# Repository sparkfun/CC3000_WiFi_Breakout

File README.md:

CC3000_WiFi_Breakout
====================

[  
*CC3000 WiFi Breakout Board (WRL-12072)*](https://www.sparkfun.com/products/12072)

WiFi breakout board for the [TI CC3000 module](http://www.ti.com/product/cc3000). The datasheet can be found [here](http://www.ti.com/lit/ds/symlink/cc3000.pdf).

Arduino library and examples can be found in the [SFE_CC3000_Library](https://github.com/sparkfun/SFE_CC3000_Library).

This part was created in Eagle v6.5.0. Example sketches were created in Arduino v1.0.5.

Repository Contents
-------------------

* **/Fritzing** - [Fritzing](http://fritzing.org/) part files
* **/Hardware** - All Eagle design files (.brd, .sch, .STL)
* **/Production** - Test bed files and production panel files

Version History
---------------
* **v1.0** Initial release

License Information
-------------------
The hardware is released under [Creative Commons Share-alike 3.0](http://creativecommons.org/licenses/by-sa/3.0/).  
All other code is open source so please feel free to do anything you want with it; you buy me a beer if you use this and we meet someday ([Beerware license](http://en.wikipedia.org/wiki/Beerware)).

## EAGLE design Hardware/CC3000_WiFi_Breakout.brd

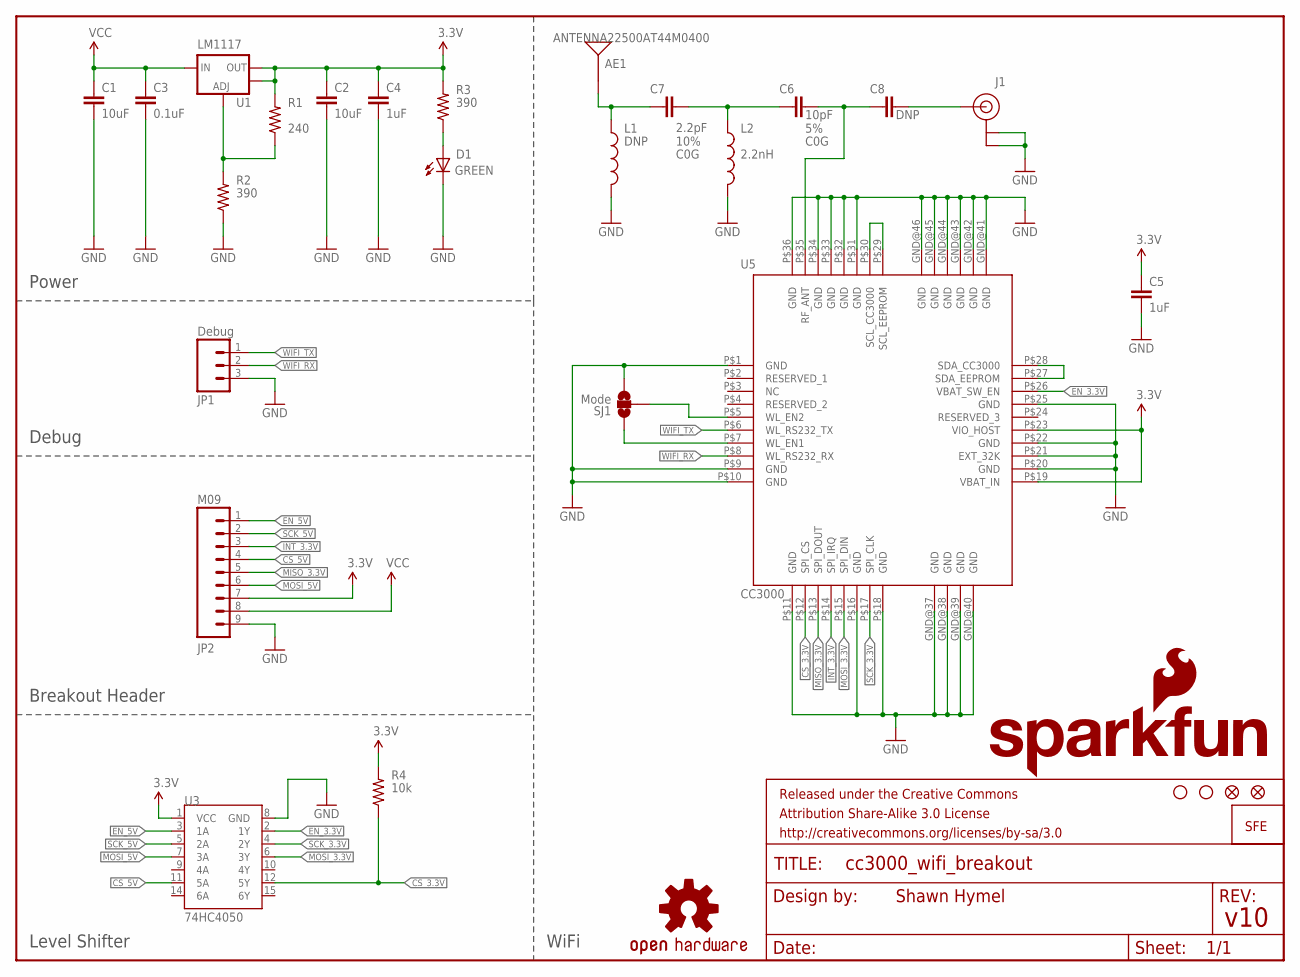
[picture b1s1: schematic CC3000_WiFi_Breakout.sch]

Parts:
AE1: ANTENNA22500AT44M0400; ANTENNA-CHIP_2500AT44M0400
C1, C2: 10uF; 0805
C3: 0.1uF; 0603-CAP
C4, C5: 1uF; 0805
C6: 10pF; 0603-CAP
C7: 2.2pF; 0603-CAP
C8: DNP; 0603-CAP
D1: GREEN; LED-0603
FID1, FID2: FIDUCIAL1X2; FIDUCIAL-1X2
FRAME1: FRAME-LETTER; CREATIVE_COMMONS
J1: U.FL
JP1: Debug; 1X03
JP2: M09; 1X09
L1: DNP; 0603
L2: 2.2nH; 0603
LOGO1: OSHW-LOGOS; OSHW-LOGO-S
LOGO3: LOGO-SFESK; SFE-LOGO-FLAME
LOGO4: SFE_LOGO_NAME_FLAME.1_INCH; SFE_LOGO_NAME_FLAME_.1
R1: 240; 0603-RES
R2, R3: 390; 0603-RES
R4: 10k; 0603-RES
SJ1: Mode; SJ_3_PASTE1&2
STANDOFF1, STANDOFF2: STAND-OFF
U1: LM1117; SOT223
U3: 74HC4050; SO016
U5: CC3000; QFN-46_CC3000

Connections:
3.3V: C2.1, C4.1, C5.1, JP2.7, R1.2, R3.2, R4.2, U1.2 (OUT), U1.4 (OUT), U3.1 (VCC), U5.P$19 (VBAT_IN), U5.P$23 (VIO_HOST)
CS_3.3V: R4.1, U3.12 (5Y), U5.P$12 (SPI_CS)
CS_5V: JP2.4, U3.11 (5A)
EN_3.3V: U3.2 (1Y), U5.P$26 (VBAT_SW_EN)
EN_5V: JP2.1, U3.3 (1A)
GND: C1.2, C2.2, C3.2, C4.2, C5.2, D1.C, J1.P$1 (GND), J1.P$2 (GND), JP1.3, JP2.9, L1.2, L2.2, R2.1, SJ1.3, U3.8 (GND), U5.GND@37 (GND), U5.GND@38 (GND), U5.GND@39 (GND), U5.GND@40 (GND), U5.GND@41 (GND), U5.GND@42 (GND), U5.GND@43 (GND), U5.GND@44 (GND), U5.GND@45 (GND), U5.GND@46 (GND), U5.P$1 (GND), U5.P$9 (GND), U5.P$10 (GND), U5.P$11 (GND), U5.P$16 (GND), U5.P$18 (GND), U5.P$20 (GND), U5.P$21 (EXT_32K), U5.P$22 (GND), U5.P$25 (GND), U5.P$31 (GND), U5.P$32 (GND), U5.P$33 (GND), U5.P$34 (GND), U5.P$36 (GND)
INT_3.3V: JP2.3, U5.P$14 (SPI_IRQ)
MISO_3.3V: JP2.5, U5.P$13 (SPI_DOUT)
MOSI_3.3V: U3.6 (3Y), U5.P$15 (SPI_DIN)
MOSI_5V: JP2.6, U3.7 (3A)
unnamed: R1.1, R2.2, U1.1 (ADJ)
unnamed: SJ1.2, U5.P$5 (WL_EN2)
unnamed: SJ1.1, U5.P$7 (WL_EN1)
unnamed: C6.1, C7.2, L2.1
unnamed: U5.P$27 (SDA_EEPROM), U5.P$28 (SDA_CC3000)
unnamed: U5.P$29 (SCL_EEPROM), U5.P$30 (SCL_CC3000)
unnamed: C6.2, C8.1, U5.P$35 (RF_ANT)
unnamed: C8.2, J1.P$3 (SIGNAL)
unnamed: AE1.FEED, C7.1, L1.1
unnamed: D1.A, R3.1
SCK_3.3V: U3.4 (2Y), U5.P$17 (SPI_CLK)
SCK_5V: JP2.2, U3.5 (2A)
VCC: C1.1, C3.1, JP2.8, U1.3 (IN)
WIFI_RX: JP1.2, U5.P$8 (WL_RS232_RX)
WIFI_TX: JP1.1, U5.P$6 (WL_RS232_TX)

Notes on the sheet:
Shawn Hymel
v10
Power
Debug
Breakout Header
Level Shifter
WiFi

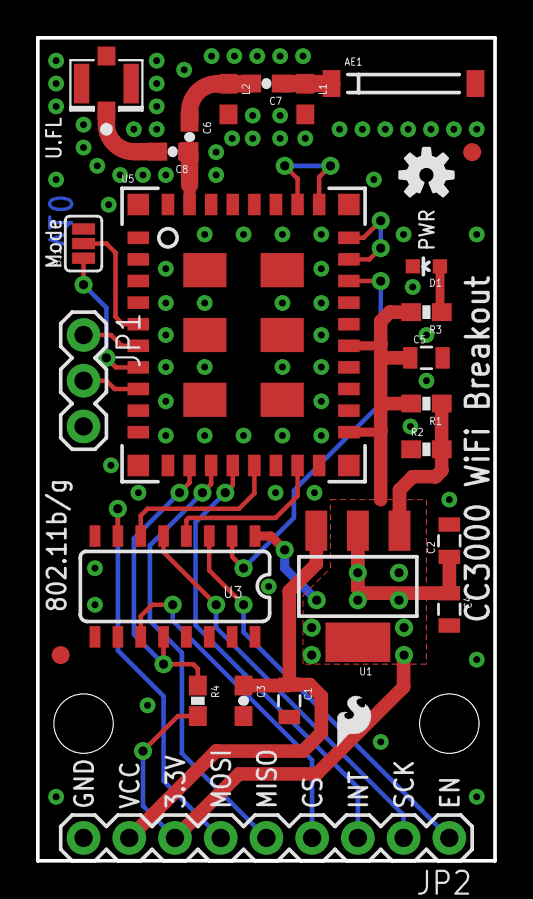
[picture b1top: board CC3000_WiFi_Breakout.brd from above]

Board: 2 copper layers, 25.4 x 45.7 mm, 31 parts (1 on the bottom side), 25 nets.

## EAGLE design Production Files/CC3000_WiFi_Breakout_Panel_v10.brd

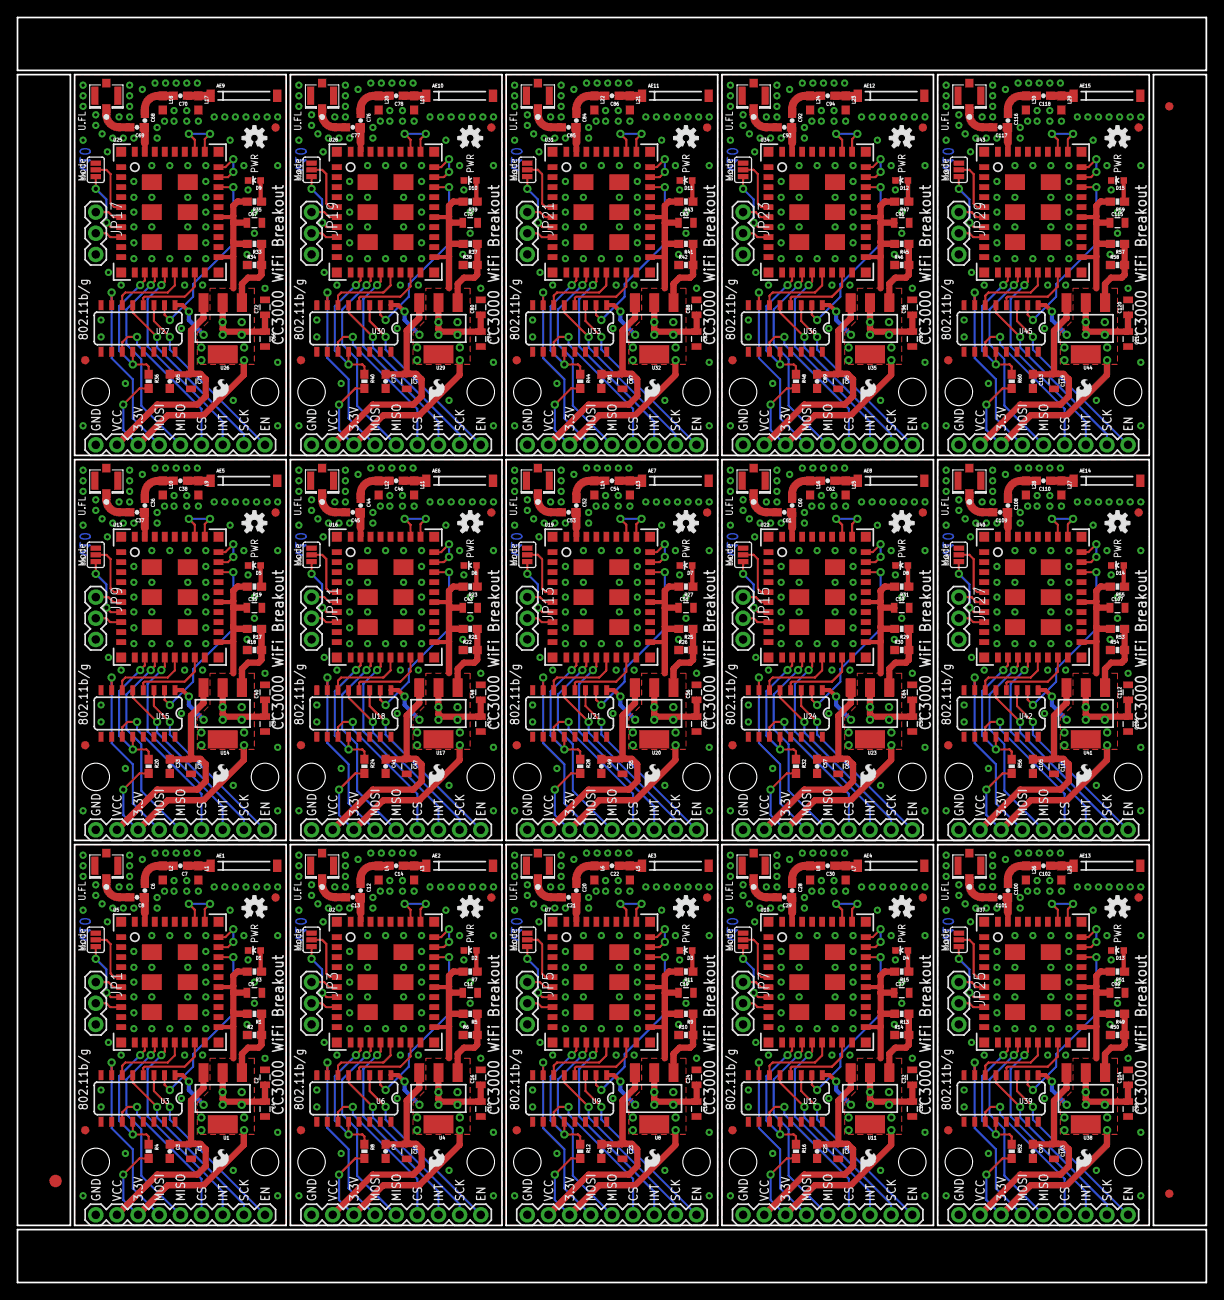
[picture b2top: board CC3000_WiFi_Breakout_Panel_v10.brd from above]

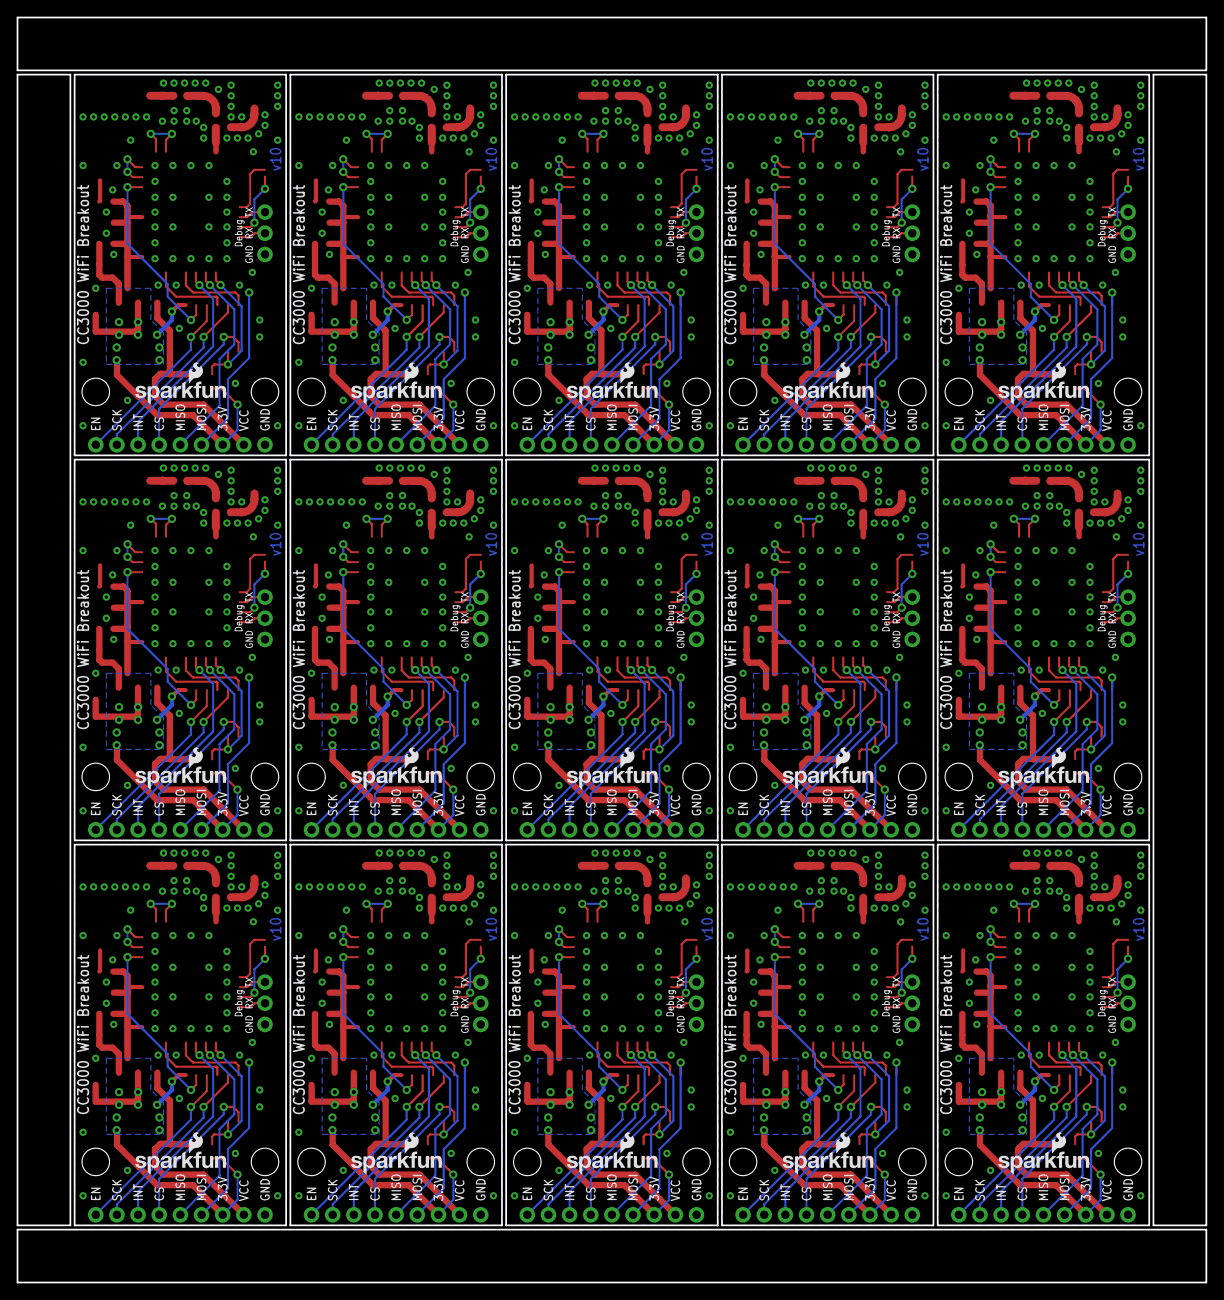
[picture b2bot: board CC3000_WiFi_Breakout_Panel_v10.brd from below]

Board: 2 copper layers, 142.7 x 151.9 mm, 453 parts (15 on the bottom side), 375 nets.

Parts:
AE1, AE2, AE3, AE4, AE5, AE6, AE7, AE8, AE9, AE10, AE11, AE12, AE13, AE14, AE15: ANTENNA22500AT44M0400; ANTENNA-CHIP_2500AT44M0400
C1, C2, C15, C16, C23, C24, C31, C32, C39, C40, C47, C48, C55, C56, C63, C64, C71, C72, C79, C80, C87, C88, C95, C96, C103, C104, C111, C112, C119, C120: 10uF; 0805
C3, C9, C17, C25, C33, C41, C49, C57, C65, C73, C81, C89, C97, C105, C113: 0.1uF; 0603-CAP
C4, C5, C10, C11, C18, C19, C26, C27, C34, C35, C42, C43, C50, C51, C58, C59, C66, C67, C74, C75, C82, C83, C90, C91, C98, C99, C106, C107, C114, C115: 1uF; 0805
C6, C12, C20, C28, C36, C44, C52, C60, C68, C76, C84, C92, C100, C108, C116: 10pF; 0603-CAP
C7, C14, C22, C30, C38, C46, C54, C62, C70, C78, C86, C94, C102, C110, C118: 2.2pF; 0603-CAP
C8, C13, C21, C29, C37, C45, C53, C61, C69, C77, C85, C93, C101, C109, C117: DNP; 0603-CAP
D1, D2, D3, D4, D5, D6, D7, D8, D9, D10, D11, D12, D13, D14, D15: GREEN; LED-0603
E$1: FIDUCIAL-1.5X3
E$4, E$6: FIDUCIAL-1X2
FID1, FID2, FID3, FID4, FID5, FID6, FID7, FID8, FID9, FID10, FID11, FID12, FID13, FID14, FID15, FID16, FID17, FID18, FID19, FID20, FID21, FID22, FID23, FID24, FID25, FID26, FID27, FID28, FID29, FID30: FIDUCIAL1X2; FIDUCIAL-1X2
J1, J2, J3, J4, J5, J6, J7, J8, J9, J10, J11, J12, J13, J14, J15: U.FL
JP1, JP3, JP5, JP7, JP9, JP11, JP13, JP15, JP17, JP19, JP21, JP23, JP25, JP27, JP29: Debug; 1X03
JP2, JP4, JP6, JP8, JP10, JP12, JP14, JP16, JP18, JP20, JP22, JP24, JP26, JP28, JP30: M09; 1X09
L1, L3, L5, L7, L9, L11, L13, L15, L17, L19, L21, L23, L25, L27, L29: DNP; 0603
L2, L4, L6, L8, L10, L12, L14, L16, L18, L20, L22, L24, L26, L28, L30: 2.2nH; 0603
LOGO1, LOGO2, LOGO7, LOGO10, LOGO13, LOGO16, LOGO19, LOGO22, LOGO25, LOGO28, LOGO31, LOGO34, LOGO37, LOGO40, LOGO43: OSHW-LOGOS; OSHW-LOGO-S
LOGO3, LOGO5, LOGO8, LOGO11, LOGO14, LOGO17, LOGO20, LOGO23, LOGO26, LOGO29, LOGO32, LOGO35, LOGO38, LOGO41, LOGO44: LOGO-SFESK; SFE-LOGO-FLAME
LOGO4, LOGO6, LOGO9, LOGO12, LOGO15, LOGO18, LOGO21, LOGO24, LOGO27, LOGO30, LOGO33, LOGO36, LOGO39, LOGO42, LOGO45: SFE_LOGO_NAME_FLAME.1_INCH; SFE_LOGO_NAME_FLAME_.1
R1, R5, R9, R13, R17, R21, R25, R29, R33, R37, R41, R45, R49, R53, R57: 240; 0603-RES
R2, R3, R6, R7, R10, R11, R14, R15, R18, R19, R22, R23, R26, R27, R30, R31, R34, R35, R38, R39, R42, R43, R46, R47, R50, R51, R54, R55, R58, R59: 390; 0603-RES
R4, R8, R12, R16, R20, R24, R28, R32, R36, R40, R44, R48, R52, R56, R60: 10k; 0603-RES
SJ1, SJ2, SJ3, SJ4, SJ5, SJ6, SJ7, SJ8, SJ9, SJ10, SJ11, SJ12, SJ13, SJ14, SJ15: Mode; SJ_3_PASTE1&2
STANDOFF1, STANDOFF2, STANDOFF3, STANDOFF4, STANDOFF5, STANDOFF6, STANDOFF7, STANDOFF8, STANDOFF9, STANDOFF10, STANDOFF11, STANDOFF12, STANDOFF13, STANDOFF14, STANDOFF15, STANDOFF16, STANDOFF17, STANDOFF18, STANDOFF19, STANDOFF20, STANDOFF21, STANDOFF22, STANDOFF23, STANDOFF24, STANDOFF25, STANDOFF26, STANDOFF27, STANDOFF28, STANDOFF29, STANDOFF30: STAND-OFF
U1, U4, U8, U11, U14, U17, U20, U23, U26, U29, U32, U35, U38, U41, U44: LM1117; SOT223
U2, U5, U7, U10, U13, U16, U19, U22, U25, U28, U31, U34, U37, U40, U43: CC3000; QFN-46_CC3000
U3, U6, U9, U12, U15, U18, U21, U24, U27, U30, U33, U36, U39, U42, U45: 74HC4050; SO016

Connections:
3.3V: C2.1, C4.1, C5.1, JP2.7, R1.2, R3.2, R4.2, U1.2, U1.4, U3.1, U5.P$19, U5.P$23
3.3V1: C10.1, C11.1, C16.1, JP4.7, R5.2, R7.2, R8.2, U2.P$19, U2.P$23, U4.2, U4.4, U6.1
3.3V2: C18.1, C19.1, C24.1, JP6.7, R9.2, R11.2, R12.2, U7.P$19, U7.P$23, U8.2, U8.4, U9.1
3.3V3: C26.1, C27.1, C32.1, JP8.7, R13.2, R15.2, R16.2, U10.P$19, U10.P$23, U11.2, U11.4, U12.1
3.3V4: C34.1, C35.1, C40.1, JP10.7, R17.2, R19.2, R20.2, U13.P$19, U13.P$23, U14.2, U14.4, U15.1
3.3V5: C42.1, C43.1, C48.1, JP12.7, R21.2, R23.2, R24.2, U16.P$19, U16.P$23, U17.2, U17.4, U18.1
3.3V6: C50.1, C51.1, C56.1, JP14.7, R25.2, R27.2, R28.2, U19.P$19, U19.P$23, U20.2, U20.4, U21.1
3.3V7: C58.1, C59.1, C64.1, JP16.7, R29.2, R31.2, R32.2, U22.P$19, U22.P$23, U23.2, U23.4, U24.1
3.3V8: C66.1, C67.1, C72.1, JP18.7, R33.2, R35.2, R36.2, U25.P$19, U25.P$23, U26.2, U26.4, U27.1
3.3V9: C74.1, C75.1, C80.1, JP20.7, R37.2, R39.2, R40.2, U28.P$19, U28.P$23, U29.2, U29.4, U30.1
3.3V10: C82.1, C83.1, C88.1, JP22.7, R41.2, R43.2, R44.2, U31.P$19, U31.P$23, U32.2, U32.4, U33.1
3.3V11: C90.1, C91.1, C96.1, JP24.7, R45.2, R47.2, R48.2, U34.P$19, U34.P$23, U35.2, U35.4, U36.1
3.3V12: C98.1, C99.1, C104.1, JP26.7, R49.2, R51.2, R52.2, U37.P$19, U37.P$23, U38.2, U38.4, U39.1
3.3V13: C106.1, C107.1, C112.1, JP28.7, R53.2, R55.2, R56.2, U40.P$19, U40.P$23, U41.2, U41.4, U42.1
3.3V14: C114.1, C115.1, C120.1, JP30.7, R57.2, R59.2, R60.2, U43.P$19, U43.P$23, U44.2, U44.4, U45.1
CS_3.3V: R4.1, U3.12, U5.P$12
CS_3.3V1: R8.1, U2.P$12, U6.12
CS_3.3V2: R12.1, U7.P$12, U9.12
CS_3.3V3: R16.1, U10.P$12, U12.12
CS_3.3V4: R20.1, U13.P$12, U15.12
CS_3.3V5: R24.1, U16.P$12, U18.12
CS_3.3V6: R28.1, U19.P$12, U21.12
CS_3.3V7: R32.1, U22.P$12, U24.12
CS_3.3V8: R36.1, U25.P$12, U27.12
CS_3.3V9: R40.1, U28.P$12, U30.12
CS_3.3V10: R44.1, U31.P$12, U33.12
CS_3.3V11: R48.1, U34.P$12, U36.12
CS_3.3V12: R52.1, U37.P$12, U39.12
CS_3.3V13: R56.1, U40.P$12, U42.12
CS_3.3V14: R60.1, U43.P$12, U45.12
CS_5V: JP2.4, U3.11
CS_5V1: JP4.4, U6.11
CS_5V2: JP6.4, U9.11
CS_5V3: JP8.4, U12.11
CS_5V4: JP10.4, U15.11
CS_5V5: JP12.4, U18.11
CS_5V6: JP14.4, U21.11
CS_5V7: JP16.4, U24.11
CS_5V8: JP18.4, U27.11
CS_5V9: JP20.4, U30.11
CS_5V10: JP22.4, U33.11
CS_5V11: JP24.4, U36.11
CS_5V12: JP26.4, U39.11
CS_5V13: JP28.4, U42.11
CS_5V14: JP30.4, U45.11
EN_3.3V: U3.2, U5.P$26
EN_3.3V1: U2.P$26, U6.2
EN_3.3V2: U7.P$26, U9.2
EN_3.3V3: U10.P$26, U12.2
EN_3.3V4: U13.P$26, U15.2
EN_3.3V5: U16.P$26, U18.2
EN_3.3V6: U19.P$26, U21.2
EN_3.3V7: U22.P$26, U24.2
EN_3.3V8: U25.P$26, U27.2
EN_3.3V9: U28.P$26, U30.2
EN_3.3V10: U31.P$26, U33.2
EN_3.3V11: U34.P$26, U36.2
EN_3.3V12: U37.P$26, U39.2
EN_3.3V13: U40.P$26, U42.2
EN_3.3V14: U43.P$26, U45.2
EN_5V: JP2.1, U3.3
EN_5V1: JP4.1, U6.3
EN_5V2: JP6.1, U9.3
EN_5V3: JP8.1, U12.3
EN_5V4: JP10.1, U15.3
EN_5V5: JP12.1, U18.3
EN_5V6: JP14.1, U21.3
EN_5V7: JP16.1, U24.3
EN_5V8: JP18.1, U27.3
EN_5V9: JP20.1, U30.3
EN_5V10: JP22.1, U33.3
EN_5V11: JP24.1, U36.3
EN_5V12: JP26.1, U39.3
EN_5V13: JP28.1, U42.3
EN_5V14: JP30.1, U45.3
GND: C1.2, C2.2, C3.2, C4.2, C5.2, D1.C, J1.P$1, J1.P$2, JP1.3, JP2.9, L1.2, L2.2, R2.1, SJ1.3, U3.8, U5.GND@37, U5.GND@38, U5.GND@39, U5.GND@40, U5.GND@41, U5.GND@42, U5.GND@43, U5.GND@44, U5.GND@45, U5.GND@46, U5.P$1, U5.P$9, U5.P$10, U5.P$11, U5.P$16, U5.P$18, U5.P$20, U5.P$21, U5.P$22, U5.P$25, U5.P$31, U5.P$32, U5.P$33, U5.P$34, U5.P$36
GND1: C9.2, C10.2, C11.2, C15.2, C16.2, D2.C, J2.P$1, J2.P$2, JP3.3, JP4.9, L3.2, L4.2, R6.1, SJ2.3, U2.GND@37, U2.GND@38, U2.GND@39, U2.GND@40, U2.GND@41, U2.GND@42, U2.GND@43, U2.GND@44, U2.GND@45, U2.GND@46, U2.P$1, U2.P$9, U2.P$10, U2.P$11, U2.P$16, U2.P$18, U2.P$20, U2.P$21, U2.P$22, U2.P$25, U2.P$31, U2.P$32, U2.P$33, U2.P$34, U2.P$36, U6.8
GND2: C17.2, C18.2, C19.2, C23.2, C24.2, D3.C, J3.P$1, J3.P$2, JP5.3, JP6.9, L5.2, L6.2, R10.1, SJ3.3, U7.GND@37, U7.GND@38, U7.GND@39, U7.GND@40, U7.GND@41, U7.GND@42, U7.GND@43, U7.GND@44, U7.GND@45, U7.GND@46, U7.P$1, U7.P$9, U7.P$10, U7.P$11, U7.P$16, U7.P$18, U7.P$20, U7.P$21, U7.P$22, U7.P$25, U7.P$31, U7.P$32, U7.P$33, U7.P$34, U7.P$36, U9.8
GND3: C25.2, C26.2, C27.2, C31.2, C32.2, D4.C, J4.P$1, J4.P$2, JP7.3, JP8.9, L7.2, L8.2, R14.1, SJ4.3, U10.GND@37, U10.GND@38, U10.GND@39, U10.GND@40, U10.GND@41, U10.GND@42, U10.GND@43, U10.GND@44, U10.GND@45, U10.GND@46, U10.P$1, U10.P$9, U10.P$10, U10.P$11, U10.P$16, U10.P$18, U10.P$20, U10.P$21, U10.P$22, U10.P$25, U10.P$31, U10.P$32, U10.P$33, U10.P$34, U10.P$36, U12.8
GND4: C33.2, C34.2, C35.2, C39.2, C40.2, D5.C, J5.P$1, J5.P$2, JP9.3, JP10.9, L9.2, L10.2, R18.1, SJ5.3, U13.GND@37, U13.GND@38, U13.GND@39, U13.GND@40, U13.GND@41, U13.GND@42, U13.GND@43, U13.GND@44, U13.GND@45, U13.GND@46, U13.P$1, U13.P$9, U13.P$10, U13.P$11, U13.P$16, U13.P$18, U13.P$20, U13.P$21, U13.P$22, U13.P$25, U13.P$31, U13.P$32, U13.P$33, U13.P$34, U13.P$36, U15.8
GND5: C41.2, C42.2, C43.2, C47.2, C48.2, D6.C, J6.P$1, J6.P$2, JP11.3, JP12.9, L11.2, L12.2, R22.1, SJ6.3, U16.GND@37, U16.GND@38, U16.GND@39, U16.GND@40, U16.GND@41, U16.GND@42, U16.GND@43, U16.GND@44, U16.GND@45, U16.GND@46, U16.P$1, U16.P$9, U16.P$10, U16.P$11, U16.P$16, U16.P$18, U16.P$20, U16.P$21, U16.P$22, U16.P$25, U16.P$31, U16.P$32, U16.P$33, U16.P$34, U16.P$36, U18.8
GND6: C49.2, C50.2, C51.2, C55.2, C56.2, D7.C, J7.P$1, J7.P$2, JP13.3, JP14.9, L13.2, L14.2, R26.1, SJ7.3, U19.GND@37, U19.GND@38, U19.GND@39, U19.GND@40, U19.GND@41, U19.GND@42, U19.GND@43, U19.GND@44, U19.GND@45, U19.GND@46, U19.P$1, U19.P$9, U19.P$10, U19.P$11, U19.P$16, U19.P$18, U19.P$20, U19.P$21, U19.P$22, U19.P$25, U19.P$31, U19.P$32, U19.P$33, U19.P$34, U19.P$36, U21.8
GND7: C57.2, C58.2, C59.2, C63.2, C64.2, D8.C, J8.P$1, J8.P$2, JP15.3, JP16.9, L15.2, L16.2, R30.1, SJ8.3, U22.GND@37, U22.GND@38, U22.GND@39, U22.GND@40, U22.GND@41, U22.GND@42, U22.GND@43, U22.GND@44, U22.GND@45, U22.GND@46, U22.P$1, U22.P$9, U22.P$10, U22.P$11, U22.P$16, U22.P$18, U22.P$20, U22.P$21, U22.P$22, U22.P$25, U22.P$31, U22.P$32, U22.P$33, U22.P$34, U22.P$36, U24.8
GND8: C65.2, C66.2, C67.2, C71.2, C72.2, D9.C, J9.P$1, J9.P$2, JP17.3, JP18.9, L17.2, L18.2, R34.1, SJ9.3, U25.GND@37, U25.GND@38, U25.GND@39, U25.GND@40, U25.GND@41, U25.GND@42, U25.GND@43, U25.GND@44, U25.GND@45, U25.GND@46, U25.P$1, U25.P$9, U25.P$10, U25.P$11, U25.P$16, U25.P$18, U25.P$20, U25.P$21, U25.P$22, U25.P$25, U25.P$31, U25.P$32, U25.P$33, U25.P$34, U25.P$36, U27.8
GND9: C73.2, C74.2, C75.2, C79.2, C80.2, D10.C, J10.P$1, J10.P$2, JP19.3, JP20.9, L19.2, L20.2, R38.1, SJ10.3, U28.GND@37, U28.GND@38, U28.GND@39, U28.GND@40, U28.GND@41, U28.GND@42, U28.GND@43, U28.GND@44, U28.GND@45, U28.GND@46, U28.P$1, U28.P$9, U28.P$10, U28.P$11, U28.P$16, U28.P$18, U28.P$20, U28.P$21, U28.P$22, U28.P$25, U28.P$31, U28.P$32, U28.P$33, U28.P$34, U28.P$36, U30.8
GND10: C81.2, C82.2, C83.2, C87.2, C88.2, D11.C, J11.P$1, J11.P$2, JP21.3, JP22.9, L21.2, L22.2, R42.1, SJ11.3, U31.GND@37, U31.GND@38, U31.GND@39, U31.GND@40, U31.GND@41, U31.GND@42, U31.GND@43, U31.GND@44, U31.GND@45, U31.GND@46, U31.P$1, U31.P$9, U31.P$10, U31.P$11, U31.P$16, U31.P$18, U31.P$20, U31.P$21, U31.P$22, U31.P$25, U31.P$31, U31.P$32, U31.P$33, U31.P$34, U31.P$36, U33.8
GND11: C89.2, C90.2, C91.2, C95.2, C96.2, D12.C, J12.P$1, J12.P$2, JP23.3, JP24.9, L23.2, L24.2, R46.1, SJ12.3, U34.GND@37, U34.GND@38, U34.GND@39, U34.GND@40, U34.GND@41, U34.GND@42, U34.GND@43, U34.GND@44, U34.GND@45, U34.GND@46, U34.P$1, U34.P$9, U34.P$10, U34.P$11, U34.P$16, U34.P$18, U34.P$20, U34.P$21, U34.P$22, U34.P$25, U34.P$31, U34.P$32, U34.P$33, U34.P$34, U34.P$36, U36.8
GND12: C97.2, C98.2, C99.2, C103.2, C104.2, D13.C, J13.P$1, J13.P$2, JP25.3, JP26.9, L25.2, L26.2, R50.1, SJ13.3, U37.GND@37, U37.GND@38, U37.GND@39, U37.GND@40, U37.GND@41, U37.GND@42, U37.GND@43, U37.GND@44, U37.GND@45, U37.GND@46, U37.P$1, U37.P$9, U37.P$10, U37.P$11, U37.P$16, U37.P$18, U37.P$20, U37.P$21, U37.P$22, U37.P$25, U37.P$31, U37.P$32, U37.P$33, U37.P$34, U37.P$36, U39.8
GND13: C105.2, C106.2, C107.2, C111.2, C112.2, D14.C, J14.P$1, J14.P$2, JP27.3, JP28.9, L27.2, L28.2, R54.1, SJ14.3, U40.GND@37, U40.GND@38, U40.GND@39, U40.GND@40, U40.GND@41, U40.GND@42, U40.GND@43, U40.GND@44, U40.GND@45, U40.GND@46, U40.P$1, U40.P$9, U40.P$10, U40.P$11, U40.P$16, U40.P$18, U40.P$20, U40.P$21, U40.P$22, U40.P$25, U40.P$31, U40.P$32, U40.P$33, U40.P$34, U40.P$36, U42.8
GND14: C113.2, C114.2, C115.2, C119.2, C120.2, D15.C, J15.P$1, J15.P$2, JP29.3, JP30.9, L29.2, L30.2, R58.1, SJ15.3, U43.GND@37, U43.GND@38, U43.GND@39, U43.GND@40, U43.GND@41, U43.GND@42, U43.GND@43, U43.GND@44, U43.GND@45, U43.GND@46, U43.P$1, U43.P$9, U43.P$10, U43.P$11, U43.P$16, U43.P$18, U43.P$20, U43.P$21, U43.P$22, U43.P$25, U43.P$31, U43.P$32, U43.P$33, U43.P$34, U43.P$36, U45.8
INT_3.3V: JP2.3, U5.P$14
INT_3.3V1: JP4.3, U2.P$14
INT_3.3V2: JP6.3, U7.P$14
INT_3.3V3: JP8.3, U10.P$14
INT_3.3V4: JP10.3, U13.P$14
INT_3.3V5: JP12.3, U16.P$14
INT_3.3V6: JP14.3, U19.P$14
INT_3.3V7: JP16.3, U22.P$14
INT_3.3V8: JP18.3, U25.P$14
INT_3.3V9: JP20.3, U28.P$14
INT_3.3V10: JP22.3, U31.P$14
INT_3.3V11: JP24.3, U34.P$14
INT_3.3V12: JP26.3, U37.P$14
INT_3.3V13: JP28.3, U40.P$14
INT_3.3V14: JP30.3, U43.P$14
MISO_3.3V: JP2.5, U5.P$13
MISO_3.3V1: JP4.5, U2.P$13
MISO_3.3V2: JP6.5, U7.P$13
MISO_3.3V3: JP8.5, U10.P$13
MISO_3.3V4: JP10.5, U13.P$13
MISO_3.3V5: JP12.5, U16.P$13
MISO_3.3V6: JP14.5, U19.P$13
MISO_3.3V7: JP16.5, U22.P$13
MISO_3.3V8: JP18.5, U25.P$13
MISO_3.3V9: JP20.5, U28.P$13
MISO_3.3V10: JP22.5, U31.P$13
MISO_3.3V11: JP24.5, U34.P$13
MISO_3.3V12: JP26.5, U37.P$13
MISO_3.3V13: JP28.5, U40.P$13
MISO_3.3V14: JP30.5, U43.P$13
MOSI_3.3V: U3.6, U5.P$15
MOSI_3.3V1: U2.P$15, U6.6
MOSI_3.3V2: U7.P$15, U9.6
MOSI_3.3V3: U10.P$15, U12.6
MOSI_3.3V4: U13.P$15, U15.6
MOSI_3.3V5: U16.P$15, U18.6
MOSI_3.3V6: U19.P$15, U21.6
MOSI_3.3V7: U22.P$15, U24.6
MOSI_3.3V8: U25.P$15, U27.6
MOSI_3.3V9: U28.P$15, U30.6
MOSI_3.3V10: U31.P$15, U33.6
MOSI_3.3V11: U34.P$15, U36.6
MOSI_3.3V12: U37.P$15, U39.6
MOSI_3.3V13: U40.P$15, U42.6
MOSI_3.3V14: U43.P$15, U45.6
MOSI_5V: JP2.6, U3.7
MOSI_5V1: JP4.6, U6.7
MOSI_5V2: JP6.6, U9.7
MOSI_5V3: JP8.6, U12.7
MOSI_5V4: JP10.6, U15.7
MOSI_5V5: JP12.6, U18.7
MOSI_5V6: JP14.6, U21.7
MOSI_5V7: JP16.6, U24.7
MOSI_5V8: JP18.6, U27.7
MOSI_5V9: JP20.6, U30.7
MOSI_5V10: JP22.6, U33.7
MOSI_5V11: JP24.6, U36.7
MOSI_5V12: JP26.6, U39.7
MOSI_5V13: JP28.6, U42.7
MOSI_5V14: JP30.6, U45.7
unnamed: R1.1, R2.2, U1.1
unnamed: SJ1.2, U5.P$5
unnamed: SJ1.1, U5.P$7
unnamed: C6.1, C7.2, L2.1
unnamed: U5.P$27, U5.P$28
unnamed: U5.P$29, U5.P$30
unnamed: C6.2, C8.1, U5.P$35
unnamed: C8.2, J1.P$3
unnamed: AE1.FEED, C7.1, L1.1
unnamed: D1.A, R3.1
unnamed: R5.1, R6.2, U4.1
unnamed: SJ2.2, U2.P$5
unnamed: SJ2.1, U2.P$7
unnamed: U2.P$27, U2.P$28
unnamed: U2.P$29, U2.P$30
unnamed: C12.1, C14.2, L4.1
unnamed: AE2.FEED, C14.1, L3.1
unnamed: C13.2, J2.P$3
unnamed: D2.A, R7.1
unnamed: C12.2, C13.1, U2.P$35
unnamed: R9.1, R10.2, U8.1
unnamed: SJ3.2, U7.P$5
unnamed: SJ3.1, U7.P$7
unnamed: U7.P$27, U7.P$28
unnamed: U7.P$29, U7.P$30
unnamed: C20.1, C22.2, L6.1
unnamed: AE3.FEED, C22.1, L5.1
unnamed: C21.2, J3.P$3
unnamed: D3.A, R11.1
unnamed: C20.2, C21.1, U7.P$35
unnamed: R13.1, R14.2, U11.1
unnamed: SJ4.2, U10.P$5
unnamed: SJ4.1, U10.P$7
unnamed: U10.P$27, U10.P$28
unnamed: U10.P$29, U10.P$30
unnamed: C28.1, C30.2, L8.1
unnamed: AE4.FEED, C30.1, L7.1
unnamed: C29.2, J4.P$3
unnamed: D4.A, R15.1
unnamed: C28.2, C29.1, U10.P$35
unnamed: R17.1, R18.2, U14.1
unnamed: SJ5.2, U13.P$5
unnamed: SJ5.1, U13.P$7
unnamed: U13.P$27, U13.P$28
unnamed: U13.P$29, U13.P$30
unnamed: C36.1, C38.2, L10.1
unnamed: AE5.FEED, C38.1, L9.1
unnamed: C37.2, J5.P$3
unnamed: D5.A, R19.1
unnamed: C36.2, C37.1, U13.P$35
unnamed: R21.1, R22.2, U17.1
unnamed: SJ6.2, U16.P$5
unnamed: SJ6.1, U16.P$7
unnamed: U16.P$27, U16.P$28
unnamed: U16.P$29, U16.P$30
unnamed: C44.1, C46.2, L12.1
unnamed: AE6.FEED, C46.1, L11.1
unnamed: C45.2, J6.P$3
unnamed: D6.A, R23.1
unnamed: C44.2, C45.1, U16.P$35
unnamed: R25.1, R26.2, U20.1
unnamed: SJ7.2, U19.P$5
unnamed: SJ7.1, U19.P$7
unnamed: U19.P$27, U19.P$28
unnamed: U19.P$29, U19.P$30
unnamed: C52.1, C54.2, L14.1
unnamed: AE7.FEED, C54.1, L13.1
unnamed: C53.2, J7.P$3
unnamed: D7.A, R27.1
unnamed: C52.2, C53.1, U19.P$35
unnamed: R29.1, R30.2, U23.1
unnamed: SJ8.2, U22.P$5
unnamed: SJ8.1, U22.P$7
unnamed: U22.P$27, U22.P$28
unnamed: U22.P$29, U22.P$30
unnamed: C60.1, C62.2, L16.1
unnamed: AE8.FEED, C62.1, L15.1
unnamed: C61.2, J8.P$3
unnamed: D8.A, R31.1
unnamed: C60.2, C61.1, U22.P$35
unnamed: R33.1, R34.2, U26.1
unnamed: SJ9.2, U25.P$5
unnamed: SJ9.1, U25.P$7
unnamed: U25.P$27, U25.P$28
unnamed: U25.P$29, U25.P$30
unnamed: C68.1, C70.2, L18.1
unnamed: AE9.FEED, C70.1, L17.1
unnamed: C69.2, J9.P$3
unnamed: D9.A, R35.1
unnamed: C68.2, C69.1, U25.P$35
unnamed: R37.1, R38.2, U29.1
unnamed: SJ10.2, U28.P$5
unnamed: SJ10.1, U28.P$7
unnamed: U28.P$27, U28.P$28
unnamed: U28.P$29, U28.P$30
unnamed: C76.1, C78.2, L20.1
unnamed: AE10.FEED, C78.1, L19.1
unnamed: C77.2, J10.P$3
unnamed: D10.A, R39.1
unnamed: C76.2, C77.1, U28.P$35
unnamed: R41.1, R42.2, U32.1
unnamed: SJ11.2, U31.P$5
unnamed: SJ11.1, U31.P$7
unnamed: U31.P$27, U31.P$28
unnamed: U31.P$29, U31.P$30
unnamed: C84.1, C86.2, L22.1
unnamed: AE11.FEED, C86.1, L21.1
unnamed: C85.2, J11.P$3
unnamed: D11.A, R43.1
unnamed: C84.2, C85.1, U31.P$35
unnamed: R45.1, R46.2, U35.1
unnamed: SJ12.2, U34.P$5
unnamed: SJ12.1, U34.P$7
unnamed: U34.P$27, U34.P$28
unnamed: U34.P$29, U34.P$30
unnamed: C92.1, C94.2, L24.1
unnamed: AE12.FEED, C94.1, L23.1
unnamed: C93.2, J12.P$3
unnamed: D12.A, R47.1
unnamed: C92.2, C93.1, U34.P$35
unnamed: R49.1, R50.2, U38.1
unnamed: SJ13.2, U37.P$5
unnamed: SJ13.1, U37.P$7
unnamed: U37.P$27, U37.P$28
unnamed: U37.P$29, U37.P$30
unnamed: C100.1, C102.2, L26.1
unnamed: AE13.FEED, C102.1, L25.1
unnamed: C101.2, J13.P$3
unnamed: D13.A, R51.1
unnamed: C100.2, C101.1, U37.P$35
unnamed: R53.1, R54.2, U41.1
unnamed: SJ14.2, U40.P$5
unnamed: SJ14.1, U40.P$7
unnamed: U40.P$27, U40.P$28
unnamed: U40.P$29, U40.P$30
unnamed: C108.1, C110.2, L28.1
unnamed: AE14.FEED, C110.1, L27.1
unnamed: C109.2, J14.P$3
unnamed: D14.A, R55.1
unnamed: C108.2, C109.1, U40.P$35
unnamed: R57.1, R58.2, U44.1
unnamed: SJ15.2, U43.P$5
unnamed: SJ15.1, U43.P$7
unnamed: U43.P$27, U43.P$28
unnamed: U43.P$29, U43.P$30
unnamed: C116.1, C118.2, L30.1
unnamed: AE15.FEED, C118.1, L29.1
unnamed: C117.2, J15.P$3
unnamed: D15.A, R59.1
unnamed: C116.2, C117.1, U43.P$35
SCK_3.3V: U3.4, U5.P$17
SCK_3.3V1: U2.P$17, U6.4
SCK_3.3V2: U7.P$17, U9.4
SCK_3.3V3: U10.P$17, U12.4
SCK_3.3V4: U13.P$17, U15.4
SCK_3.3V5: U16.P$17, U18.4
SCK_3.3V6: U19.P$17, U21.4
SCK_3.3V7: U22.P$17, U24.4
SCK_3.3V8: U25.P$17, U27.4
SCK_3.3V9: U28.P$17, U30.4
SCK_3.3V10: U31.P$17, U33.4
SCK_3.3V11: U34.P$17, U36.4
SCK_3.3V12: U37.P$17, U39.4
SCK_3.3V13: U40.P$17, U42.4
SCK_3.3V14: U43.P$17, U45.4
SCK_5V: JP2.2, U3.5
SCK_5V1: JP4.2, U6.5
SCK_5V2: JP6.2, U9.5
SCK_5V3: JP8.2, U12.5
SCK_5V4: JP10.2, U15.5
SCK_5V5: JP12.2, U18.5
SCK_5V6: JP14.2, U21.5
SCK_5V7: JP16.2, U24.5
SCK_5V8: JP18.2, U27.5
SCK_5V9: JP20.2, U30.5
SCK_5V10: JP22.2, U33.5
SCK_5V11: JP24.2, U36.5
SCK_5V12: JP26.2, U39.5
SCK_5V13: JP28.2, U42.5
SCK_5V14: JP30.2, U45.5
VCC: C1.1, C3.1, JP2.8, U1.3
VCC1: C9.1, C15.1, JP4.8, U4.3
VCC2: C17.1, C23.1, JP6.8, U8.3
VCC3: C25.1, C31.1, JP8.8, U11.3
VCC4: C33.1, C39.1, JP10.8, U14.3
VCC5: C41.1, C47.1, JP12.8, U17.3
VCC6: C49.1, C55.1, JP14.8, U20.3
VCC7: C57.1, C63.1, JP16.8, U23.3
VCC8: C65.1, C71.1, JP18.8, U26.3
VCC9: C73.1, C79.1, JP20.8, U29.3
VCC10: C81.1, C87.1, JP22.8, U32.3
VCC11: C89.1, C95.1, JP24.8, U35.3
VCC12: C97.1, C103.1, JP26.8, U38.3
VCC13: C105.1, C111.1, JP28.8, U41.3
VCC14: C113.1, C119.1, JP30.8, U44.3
WIFI_RX: JP1.2, U5.P$8
WIFI_RX1: JP3.2, U2.P$8
WIFI_RX2: JP5.2, U7.P$8
WIFI_RX3: JP7.2, U10.P$8
WIFI_RX4: JP9.2, U13.P$8
WIFI_RX5: JP11.2, U16.P$8
WIFI_RX6: JP13.2, U19.P$8
WIFI_RX7: JP15.2, U22.P$8
WIFI_RX8: JP17.2, U25.P$8
WIFI_RX9: JP19.2, U28.P$8
WIFI_RX10: JP21.2, U31.P$8
WIFI_RX11: JP23.2, U34.P$8
WIFI_RX12: JP25.2, U37.P$8
WIFI_RX13: JP27.2, U40.P$8
WIFI_RX14: JP29.2, U43.P$8
WIFI_TX: JP1.1, U5.P$6
WIFI_TX1: JP3.1, U2.P$6
WIFI_TX2: JP5.1, U7.P$6
WIFI_TX3: JP7.1, U10.P$6
WIFI_TX4: JP9.1, U13.P$6
WIFI_TX5: JP11.1, U16.P$6
WIFI_TX6: JP13.1, U19.P$6
WIFI_TX7: JP15.1, U22.P$6
WIFI_TX8: JP17.1, U25.P$6
WIFI_TX9: JP19.1, U28.P$6
WIFI_TX10: JP21.1, U31.P$6
WIFI_TX11: JP23.1, U34.P$6
WIFI_TX12: JP25.1, U37.P$6
WIFI_TX13: JP27.1, U40.P$6
WIFI_TX14: JP29.1, U43.P$6

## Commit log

2013-09-18 Created schematic and initial layout
2013-09-19 Layout (mostly) done
2013-09-19 Proto layout complete. Needs aesthetics.
2013-09-20 Prototype board ready for review
2013-09-23 Ready for prototype
2013-12-12 Changed layout for board
2013-12-13 Redid layout. Again.
2013-12-16 Moved headers closer to board edge
2014-01-16 Moved SS Flame down, added pin marker for U.FL in SS
2014-01-23 Added silk U.FL; adjusted tvalue markings for easier reading
2014-01-23 Created Panel
2014-03-18 Added Fritzing parts
2014-03-18 Added pdf of schematic
2014-04-03 Updated readme files
2014-04-03 Updated main readme to link to TI's CC3000 page.

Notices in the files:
parts and their libraries:
SparkFun-Aesthetics: Licensing: CC v3.0 Share-Alike You are welcome to use this library for commercial purposes.
SparkFun-Aesthetics: Released under the Creative Commons Attribution Share-Alike 3.0 License
SparkFun-Aesthetics: Released under the Creative Commons
